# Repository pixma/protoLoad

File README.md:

protoLoad
=========

protoload, which is arduino plus load cell, shows weight.

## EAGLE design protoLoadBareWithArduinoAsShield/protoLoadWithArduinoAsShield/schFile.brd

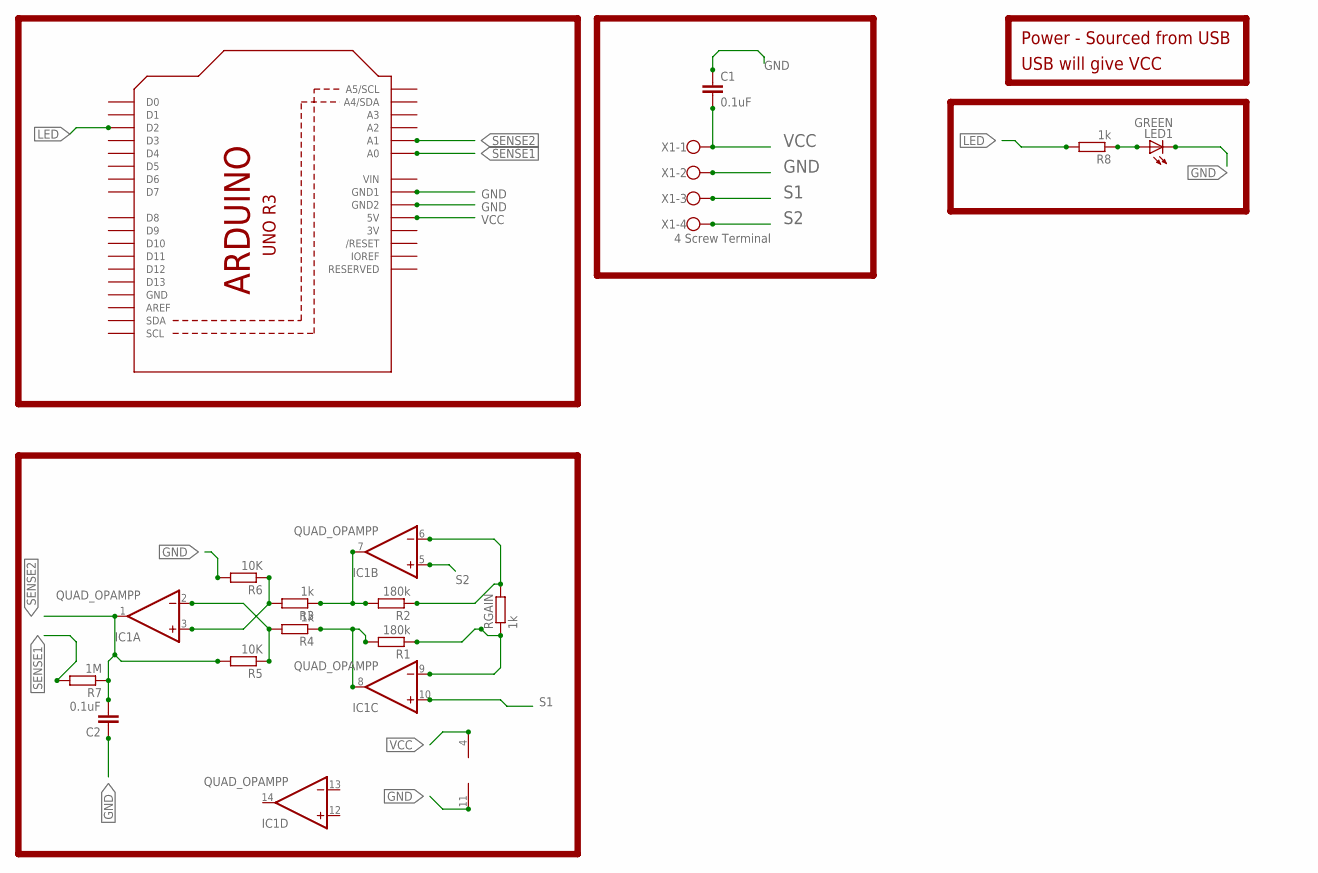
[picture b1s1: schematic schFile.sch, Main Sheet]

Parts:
ARDUINO: ARDUINOR3-BPLACE
C1, C2: 0.1uF; CAP-PTH-SMALLEZ
IC1: QUAD_OPAMPP; DIL14
LED1: GREEN; LED3MM
R1, R2: 180k; 0207/10
R3, R4, R8: 1k; 0207/10
R5, R6: 10K; 0207/10
R7: 1M; 0207/10
RGAIN: 1k; 0207/10
X1: 4 Screw Terminal; W237-4

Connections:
3V: ARDUINO.3V
GND: ARDUINO.GND, ARDUINO.GND1, ARDUINO.GND2, C1.1, C2.1, IC1.11 (V-), LED1.K (C), R6.2, X1.2
LED: ARDUINO.D2, R8.2
unnamed: IC1.7 (OUT), R2.2, R3.1
unnamed: IC1.2 (-IN), R4.2, R5.1
unnamed: IC1.9 (-IN), R1.1, RGAIN.1
unnamed: LED1.A, R8.1
unnamed: IC1.3 (+IN), R3.2, R6.1
unnamed: IC1.6 (-IN), R2.1, RGAIN.2
unnamed: IC1.8 (OUT), R1.2, R4.1
S1: IC1.10 (+IN), X1.3
S2: IC1.5 (+IN), X1.4
SENSE1: ARDUINO.A0, R7.2
SENSE2: ARDUINO.A1, C2.2, IC1.1 (OUT), R5.2, R7.1
VCC: ARDUINO.5V, C1.2, IC1.4 (V+), X1.1
VIN: ARDUINO.VIN

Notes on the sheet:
Power - Sourced from USB
USB will give VCC

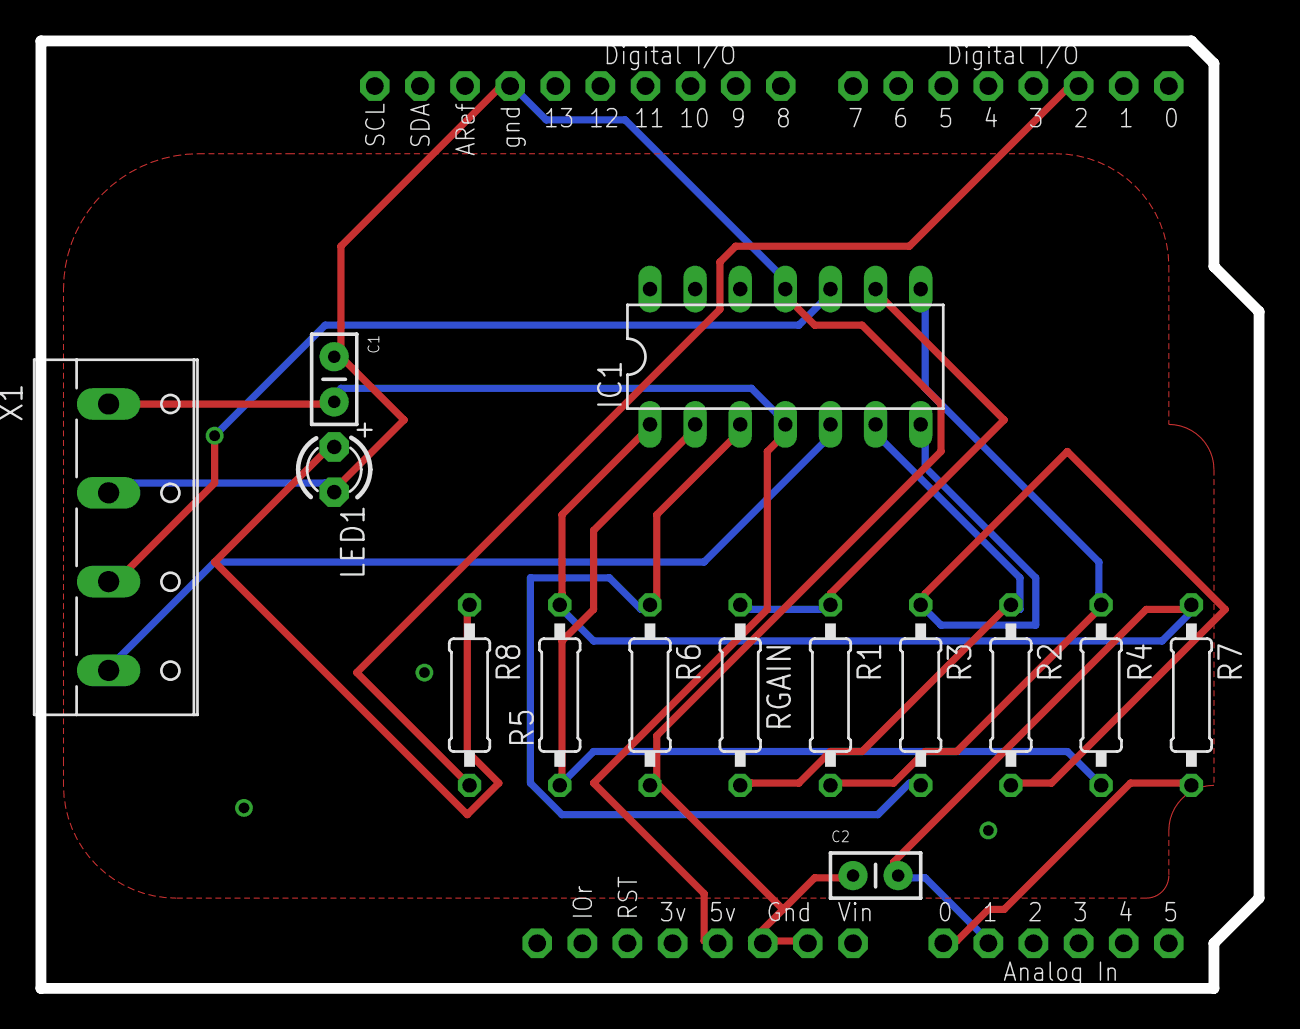
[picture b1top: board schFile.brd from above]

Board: 2 copper layers, 68.6 x 53.3 mm, 15 parts (0 on the bottom side), 14 nets.

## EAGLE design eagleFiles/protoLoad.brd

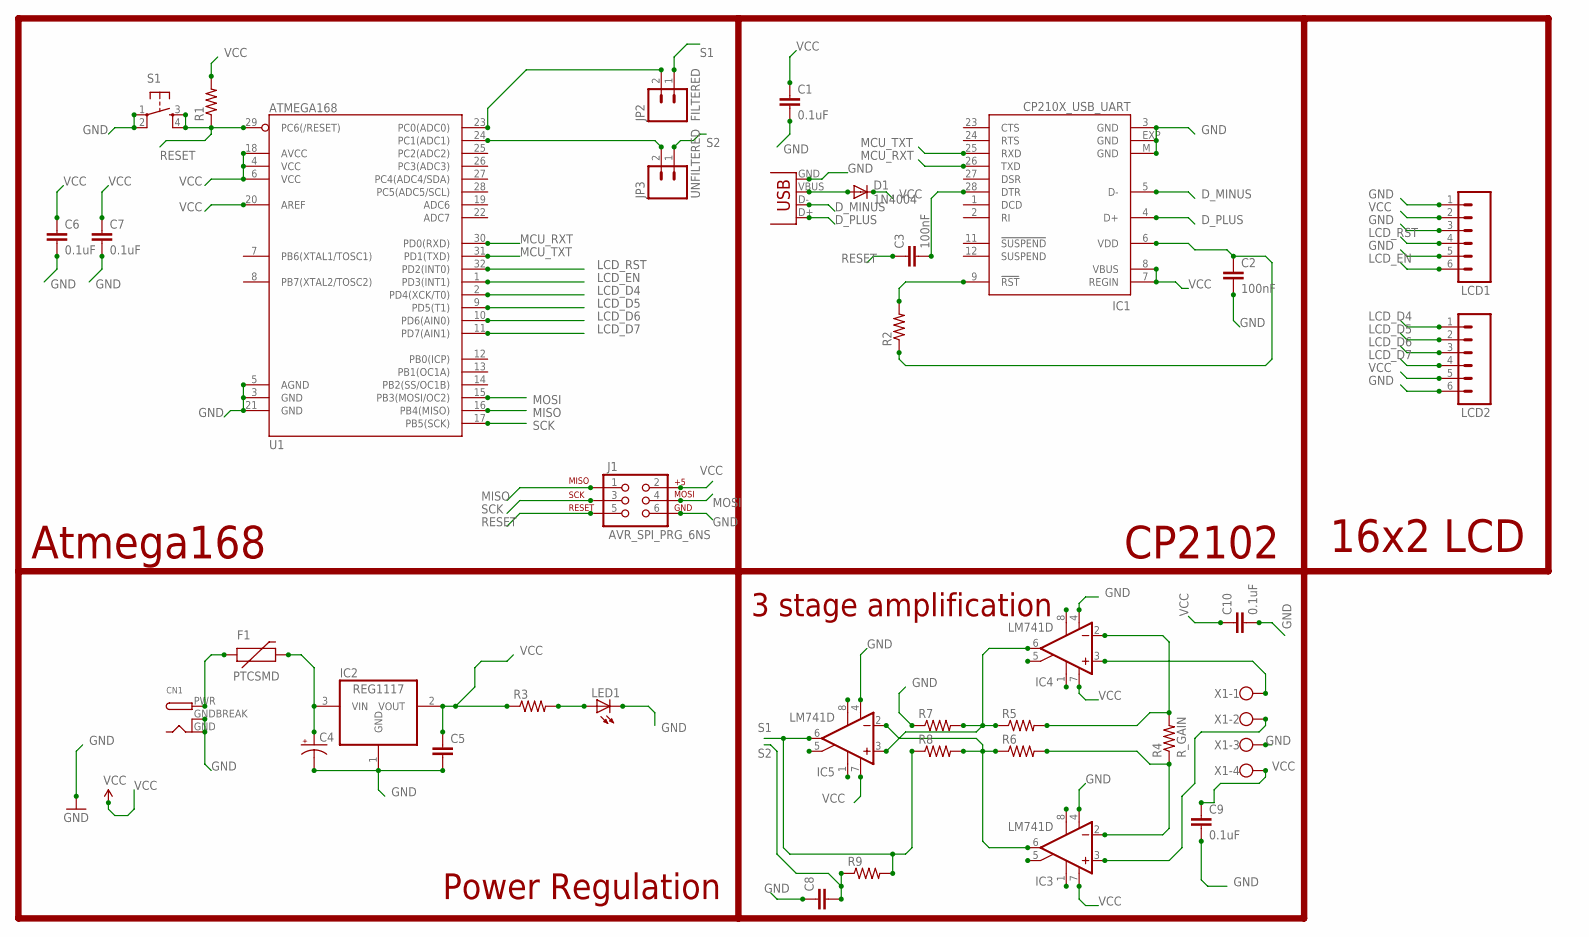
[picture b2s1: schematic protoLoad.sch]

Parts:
C1, C6, C7, C9, C10: 0.1uF; 0805
C2, C3: 100nF; 0805
C4: CAP_POL7343; EIA7343
C5, C8: CAP0805; 0805
CN1: DCBARRELPTH; DCJACK_2MM_PTH
D1: 1N4004; SMA-DIODE_ALT
F1: PTCSMD; PTC-1206
IC1: CP210X_USB_UART; MLP28
IC2: REG1117; SOT223
IC3, IC4, IC5: LM741D; SO08
J1: AVR_SPI_PRG_6NS; 2X3-NS
JP1: USBSMD; USB-MINIB
JP2: FILTERED; 1X02_LONGPADS
JP3: UNFILTERED; 1X02_LONGPADS
LCD1, LCD2: M06LONGPADS; 1X06_LONGPADS
LED1: LEDCHIPLED_1206; CHIPLED_1206
R1, R2, R3, R5, R6, R7, R8, R9: RESISTOR0805-RES; 0805
R4: R_GAIN; 0805
S1: TAC_SWITCHSMD; TACTILE_SWITCH_SMD
U1: ATMEGA168; TQFP32-08
X1: W237-4

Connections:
D_MINUS: IC1.5 (D-), JP1.D-
D_PLUS: IC1.4 (D+), JP1.D+
GND: C1.2, C2.2, C4.C (-), C5.2, C6.2, C7.2, C8.1, C9.2, C10.2, CN1.GND, CN1.GNDBREAK, IC1.3 (GND), IC1.EXP (GND), IC1.M (GND), IC2.1 (GND), IC3.4 (V-), IC4.4 (V-), IC5.4 (V-), J1.6, JP1.GND, LCD1.1, LCD1.3, LCD1.5, LCD2.6, LED1.C, R7.1, S1.1, S1.2, U1.3 (GND), U1.5 (AGND), U1.21 (GND), X1.3
LCD_D4: LCD2.1, U1.2 (PD4(XCK/T0))
LCD_D5: LCD2.2, U1.9 (PD5(T1))
LCD_D6: LCD2.3, U1.10 (PD6(AIN0))
LCD_D7: LCD2.4, U1.11 (PD7(AIN1))
LCD_EN: LCD1.6, U1.1 (PD3(INT1))
LCD_RST: LCD1.4, U1.32 (PD2(INT0))
MCU_RXT: IC1.26 (TXD), U1.30 (PD0(RXD))
MCU_TXT: IC1.25 (RXD), U1.31 (PD1(TXD))
MISO: J1.1, U1.16 (PB4(MISO))
MOSI: J1.4, U1.15 (PB3(MOSI/OC2))
unnamed: C3.2, IC1.28 (DTR)
unnamed: IC1.9 (!RST), R2.2
unnamed: D1.A, JP1.VBUS
unnamed: C2.1, IC1.6 (VDD), R2.1
unnamed: CN1.PWR, F1.1
unnamed: JP3.2, U1.24 (PC1(ADC1))
unnamed: LED1.A, R3.2
unnamed: IC4.3 (+IN), X1.1
unnamed: IC3.3 (+IN), X1.2
unnamed: JP2.2, U1.23 (PC0(ADC0))
unnamed: C4.A (+), F1.2, IC2.3 (VIN)
unnamed: IC3.6 (OUT), IC5.2 (-IN), R6.1, R8.2
unnamed: IC4.2 (-IN), R4.2, R5.2
unnamed: IC3.2 (-IN), R4.1, R6.2
unnamed: IC4.6 (OUT), IC5.3 (+IN), R5.1, R7.2
RESET: C3.1, J1.5, R1.1, S1.3, S1.4, U1.29 (PC6(/RESET))
S1: IC5.6 (OUT), JP2.1, R8.1, R9.2
S2: C8.2, JP3.1, R9.1
SCK: J1.3, U1.17 (PB5(SCK))
VCC: C1.1, C5.1, C6.1, C7.1, C9.1, C10.1, D1.C, IC1.7 (REGIN), IC1.8 (VBUS), IC2.2 (VOUT), IC3.7 (V+), IC4.7 (V+), IC5.7 (V+), J1.2, LCD1.2, LCD2.5, R1.2, R3.1, U1.4 (VCC), U1.6 (VCC), U1.18 (AVCC), U1.20 (AREF), X1.4

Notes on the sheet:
Atmega168
CP2102
Power Regulation
3 stage amplification
16x2 LCD

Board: 2 copper layers, 37 parts (5 on the bottom side), 33 nets, no tracks yet.

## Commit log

2014-03-28 first push
2014-03-28 schematics and board file, unrouted added for now
2014-03-29 added board 3d imageand little update on brd file, placements
2014-03-31 revisited schematic, no changes as such
2014-03-31 loose schematic, also help in generating bom
2014-04-01 added schematic nd board file, shield, for reference.
2014-04-01 regular push
2014-04-01 address, and updated doc file
2014-04-01 updated mail
2014-04-12 general update
2014-04-12 first push for pages
2014-05-14 normal push
2014-05-16 images, uploaded, wrecked USB pins from inside, unknown reason of occurence,and unexpected.
2014-05-16 redundant file, hence deleted.
2014-05-27 lib updated, and, this is been used.
2014-06-02 code added, for smoothening, taking avg for now.
2014-06-03 added one client Window App for connecting the protoload Device
    Require DOT NET 4.5 platform
2014-06-03 windpwApp snap added working.
2014-06-06 noral push, data point collected.

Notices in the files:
parts and their libraries:
SparkFun-DigitalIC: Licensing: Creative Commons ShareAlike 4.0 International - https://creativecommons.org/licenses/by-sa/4.0
